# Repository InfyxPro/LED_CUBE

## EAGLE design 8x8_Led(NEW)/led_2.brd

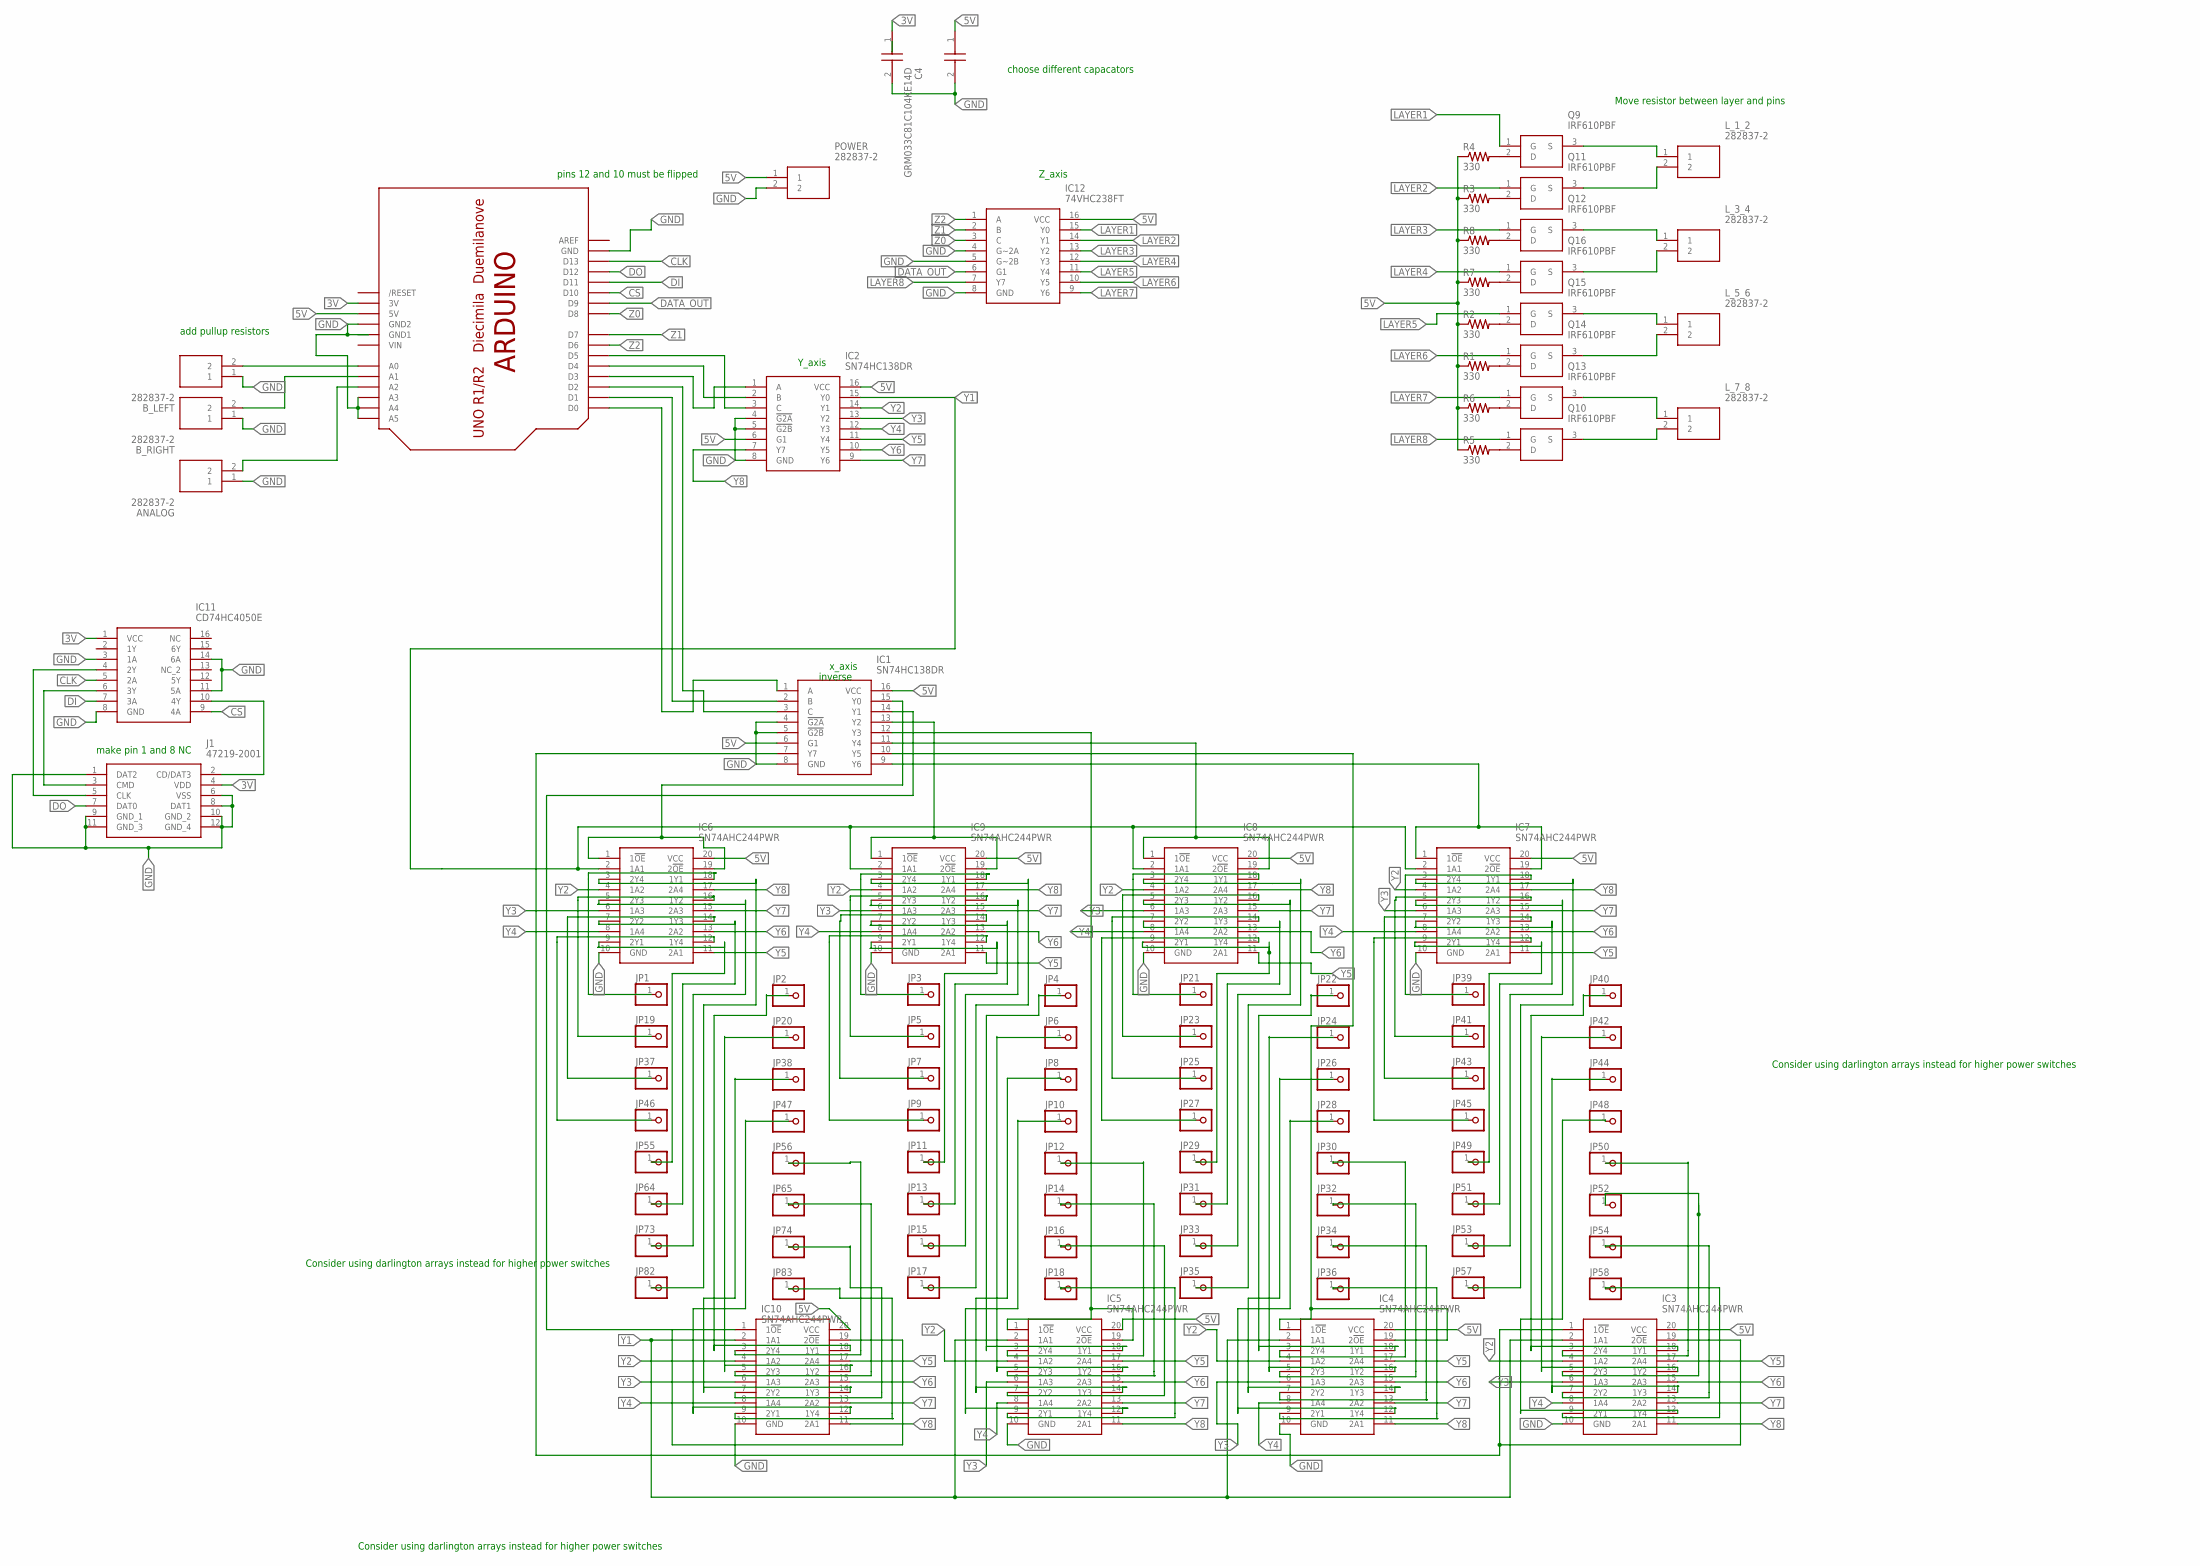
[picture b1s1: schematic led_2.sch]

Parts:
ANALOG: 282837-2; SHDR2W100P0X508_1X2_1016X820X1
B_LEFT: 282837-2; SHDR2W100P0X508_1X2_1016X820X1
B_RIGHT: 282837-2; SHDR2W100P0X508_1X2_1016X820X1
C4, C5: GRM033C81C104KE14D; CAPC0603X33N
IC1, IC2: SN74HC138DR; SOIC127P600X175-16N
IC3, IC4, IC5, IC6, IC7, IC8, IC9, IC10: SN74AHC244PWR; SOP65P640X120-20N
IC11: CD74HC4050E; DIP254P762X508-16
IC12: 74VHC238FT; SOP65P640X120-16N
J1: 47219-2001; 472192001
JP1, JP2, JP3, JP4, JP5, JP6, JP7, JP8, JP9, JP10, JP11, JP12, JP13, JP14, JP15, JP16, JP17, JP18, JP19, JP20, JP21, JP22, JP23, JP24, JP25, JP26, JP27, JP28, JP29, JP30, JP31, JP32, JP33, JP34, JP35, JP36, JP37, JP38, JP39, JP40, JP41, JP42, JP43, JP44, JP45, JP46, JP47, JP48, JP49, JP50, JP51, JP52, JP53, JP54, JP55, JP56, JP57, JP58, JP64, JP65, JP73, JP74, JP82, JP83: PINHD-1X1; 1X01
L_1_2, L_3_4, L_5_6, L_7_8: 282837-2; SHDR2W100P0X508_1X2_1016X820X1
POWER: 282837-2; SHDR2W100P0X508_1X2_1016X820X1
Q9, Q10, Q11, Q12, Q13, Q14, Q15, Q16: IRF610PBF; TO254P465X1024X2050-3P
R1, R2, R3, R4, R5, R6, R7, R8: 330; 0207/12
U$2: ARDUINO-NOHOLE

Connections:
3V: C4.1, IC11.1 (VCC), J1.4 (VDD), U$2.3V
5V: C5.1, IC1.6 (G1), IC1.16 (VCC), IC2.6 (G1), IC2.16 (VCC), IC3.20 (VCC), IC4.20 (VCC), IC5.20 (VCC), IC6.20 (VCC), IC7.20 (VCC), IC8.20 (VCC), IC9.20 (VCC), IC10.20 (VCC), IC12.16 (VCC), POWER.1, R1.1, R2.1, R3.1, R4.1, R5.1, R6.1, R7.1, R8.1, U$2.5V
CLK: IC11.5 (2A), U$2.D13
CS: IC11.9 (4A), U$2.D10
DATA_OUT: IC12.6 (G1), U$2.D9
DI: IC11.7 (3A), U$2.D11
DO: J1.7 (DAT0), U$2.D12
GND: ANALOG.1, B_LEFT.1, B_RIGHT.1, C4.2, C5.2, IC1.4 (!G2A), IC1.5 (!G2B), IC1.8 (GND), IC2.4 (!G2A), IC2.5 (!G2B), IC2.8 (GND), IC3.10 (GND), IC4.10 (GND), IC5.10 (GND), IC6.10 (GND), IC7.10 (GND), IC8.10 (GND), IC9.10 (GND), IC10.10 (GND), IC11.3 (1A), IC11.8 (GND), IC11.11 (5A), IC11.14 (6A), IC12.4 (G~2A), IC12.5 (G~2B), IC12.8 (GND), J1.1 (DAT2), J1.6 (VSS), J1.8 (DAT1), J1.9 (GND_1), J1.10 (GND_2), J1.11 (GND_3), J1.12 (GND_4), POWER.2, U$2.A3, U$2.A4, U$2.A5, U$2.GND, U$2.GND1, U$2.GND2
LAYER1: IC12.15 (Y0), Q9.1 (G)
LAYER2: IC12.14 (Y1), Q11.1 (G)
LAYER3: IC12.13 (Y2), Q12.1 (G)
LAYER4: IC12.12 (Y3), Q16.1 (G)
LAYER5: IC12.11 (Y4), Q15.1 (G)
LAYER6: IC12.10 (Y5), Q14.1 (G)
LAYER7: IC12.9 (Y6), Q13.1 (G)
LAYER8: IC12.7 (Y7), Q10.1 (G)
unnamed: IC1.9 (Y6), IC7.1 (1!OE), IC7.19 (2!OE)
unnamed: IC2.3 (C), U$2.D5
unnamed: IC6.18 (1Y1), JP1.1
unnamed: IC2.2 (B), U$2.D4
unnamed: IC6.16 (1Y2), JP19.1
unnamed: IC6.14 (1Y3), JP37.1
unnamed: IC6.12 (1Y4), JP46.1
unnamed: IC6.9 (2Y1), JP55.1
unnamed: IC6.7 (2Y2), JP64.1
unnamed: IC6.5 (2Y3), JP73.1
unnamed: IC2.1 (A), U$2.D3
unnamed: IC1.3 (C), U$2.D2
unnamed: IC1.2 (B), U$2.D1
unnamed: IC1.1 (A), U$2.D0
unnamed: B_LEFT.2, U$2.A0
unnamed: Q9.2 (D), R4.2
unnamed: Q11.2 (D), R3.2
unnamed: Q12.2 (D), R8.2
unnamed: Q16.2 (D), R7.2
unnamed: Q15.2 (D), R2.2
unnamed: Q14.2 (D), R1.2
unnamed: Q13.2 (D), R6.2
unnamed: Q10.2 (D), R5.2
unnamed: L_1_2.1, Q9.3 (S)
unnamed: L_1_2.2, Q11.3 (S)
unnamed: L_3_4.1, Q12.3 (S)
unnamed: L_3_4.2, Q16.3 (S)
unnamed: L_5_6.1, Q15.3 (S)
unnamed: L_5_6.2, Q14.3 (S)
unnamed: L_7_8.1, Q13.3 (S)
unnamed: L_7_8.2, Q10.3 (S)
unnamed: IC6.3 (2Y4), JP82.1
unnamed: IC10.18 (1Y1), JP2.1
unnamed: IC10.16 (1Y2), JP20.1
unnamed: IC10.14 (1Y3), JP38.1
unnamed: IC10.12 (1Y4), JP47.1
unnamed: IC10.3 (2Y4), JP56.1
unnamed: IC10.5 (2Y3), JP65.1
unnamed: IC10.7 (2Y2), JP74.1
unnamed: IC10.9 (2Y1), JP83.1
unnamed: IC9.18 (1Y1), JP3.1
unnamed: IC9.16 (1Y2), JP5.1
unnamed: IC9.14 (1Y3), JP7.1
unnamed: IC9.12 (1Y4), JP9.1
unnamed: IC9.9 (2Y1), JP11.1
unnamed: IC9.7 (2Y2), JP13.1
unnamed: IC9.5 (2Y3), JP15.1
unnamed: IC9.3 (2Y4), JP17.1
unnamed: IC5.18 (1Y1), JP4.1
unnamed: IC5.16 (1Y2), JP6.1
unnamed: IC5.14 (1Y3), JP8.1
unnamed: IC5.12 (1Y4), JP10.1
unnamed: IC5.3 (2Y4), JP12.1
unnamed: IC5.5 (2Y3), JP14.1
unnamed: IC5.7 (2Y2), JP16.1
unnamed: IC5.9 (2Y1), JP18.1
unnamed: IC8.18 (1Y1), JP21.1
unnamed: IC8.16 (1Y2), JP23.1
unnamed: IC8.14 (1Y3), JP25.1
unnamed: IC8.12 (1Y4), JP27.1
unnamed: IC8.9 (2Y1), JP29.1
unnamed: IC8.7 (2Y2), JP31.1
unnamed: IC8.5 (2Y3), JP33.1
unnamed: IC8.3 (2Y4), JP35.1
unnamed: IC4.18 (1Y1), JP22.1
unnamed: IC4.16 (1Y2), JP24.1
unnamed: IC4.14 (1Y3), JP26.1
unnamed: IC4.12 (1Y4), JP28.1
unnamed: IC4.3 (2Y4), JP30.1
unnamed: IC4.5 (2Y3), JP32.1
unnamed: IC4.7 (2Y2), JP34.1
unnamed: IC4.9 (2Y1), JP36.1
unnamed: IC7.18 (1Y1), JP39.1
unnamed: IC7.16 (1Y2), JP41.1
unnamed: IC7.14 (1Y3), JP43.1
unnamed: IC7.12 (1Y4), JP45.1
unnamed: IC7.9 (2Y1), JP49.1
unnamed: IC7.7 (2Y2), JP51.1
unnamed: IC7.5 (2Y3), JP53.1
unnamed: IC7.3 (2Y4), JP57.1
unnamed: IC3.18 (1Y1), JP40.1
unnamed: IC3.16 (1Y2), JP42.1
unnamed: IC3.14 (1Y3), JP44.1
unnamed: IC3.12 (1Y4), JP48.1
unnamed: IC3.3 (2Y4), JP50.1
unnamed: IC3.5 (2Y3), JP52.1
unnamed: IC3.7 (2Y2), JP54.1
unnamed: IC3.9 (2Y1), JP58.1
unnamed: IC1.15 (Y0), IC6.1 (1!OE), IC6.19 (2!OE)
unnamed: IC1.13 (Y2), IC9.1 (1!OE), IC9.19 (2!OE)
unnamed: IC1.11 (Y4), IC8.1 (1!OE), IC8.19 (2!OE)
unnamed: IC1.14 (Y1), IC10.1 (1!OE), IC10.19 (2!OE)
unnamed: IC1.7 (Y7), IC3.1 (1!OE), IC3.19 (2!OE)
unnamed: IC1.12 (Y3), IC5.1 (1!OE), IC5.19 (2!OE)
unnamed: IC1.10 (Y5), IC4.1 (1!OE), IC4.19 (2!OE)
unnamed: ANALOG.2, U$2.A2
unnamed: IC11.6 (3Y), J1.3 (CMD)
unnamed: IC11.4 (2Y), J1.5 (CLK)
unnamed: IC11.10 (4Y), J1.2 (CD/DAT3)
unnamed: B_RIGHT.2, U$2.A1
VIN: U$2.VIN
Y1: IC2.15 (Y0), IC3.2 (1A1), IC4.2 (1A1), IC5.2 (1A1), IC6.2 (1A1), IC7.2 (1A1), IC8.2 (1A1), IC9.2 (1A1), IC10.2 (1A1)
Y2: IC2.14 (Y1), IC3.4 (1A2), IC4.4 (1A2), IC5.4 (1A2), IC6.4 (1A2), IC7.4 (1A2), IC8.4 (1A2), IC9.4 (1A2), IC10.4 (1A2)
Y3: IC2.13 (Y2), IC3.6 (1A3), IC4.6 (1A3), IC5.6 (1A3), IC6.6 (1A3), IC7.6 (1A3), IC8.6 (1A3), IC9.6 (1A3), IC10.6 (1A3)
Y4: IC2.12 (Y3), IC3.8 (1A4), IC4.8 (1A4), IC5.8 (1A4), IC6.8 (1A4), IC7.8 (1A4), IC8.8 (1A4), IC9.8 (1A4), IC10.8 (1A4)
Y5: IC2.11 (Y4), IC3.17 (2A4), IC4.17 (2A4), IC5.17 (2A4), IC6.11 (2A1), IC7.11 (2A1), IC8.11 (2A1), IC9.11 (2A1), IC10.17 (2A4)
Y6: IC2.10 (Y5), IC3.15 (2A3), IC4.15 (2A3), IC5.15 (2A3), IC6.13 (2A2), IC7.13 (2A2), IC8.13 (2A2), IC9.13 (2A2), IC10.15 (2A3)
Y7: IC2.9 (Y6), IC3.13 (2A2), IC4.13 (2A2), IC5.13 (2A2), IC6.15 (2A3), IC7.15 (2A3), IC8.15 (2A3), IC9.15 (2A3), IC10.13 (2A2)
Y8: IC2.7 (Y7), IC3.11 (2A1), IC4.11 (2A1), IC5.11 (2A1), IC6.17 (2A4), IC7.17 (2A4), IC8.17 (2A4), IC9.17 (2A4), IC10.11 (2A1)
Z0: IC12.3 (C), U$2.D8
Z1: IC12.2 (B), U$2.D7
Z2: IC12.1 (A), U$2.D6

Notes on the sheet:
inverse
Y_axis
Z_axis
x_axis
pins 12 and 10 must be flipped
make pin 1 and 8 NC
add pullup resistors
choose different capacators
Move resistor between layer and pins
Consider using darlington arrays instead for higher power switches

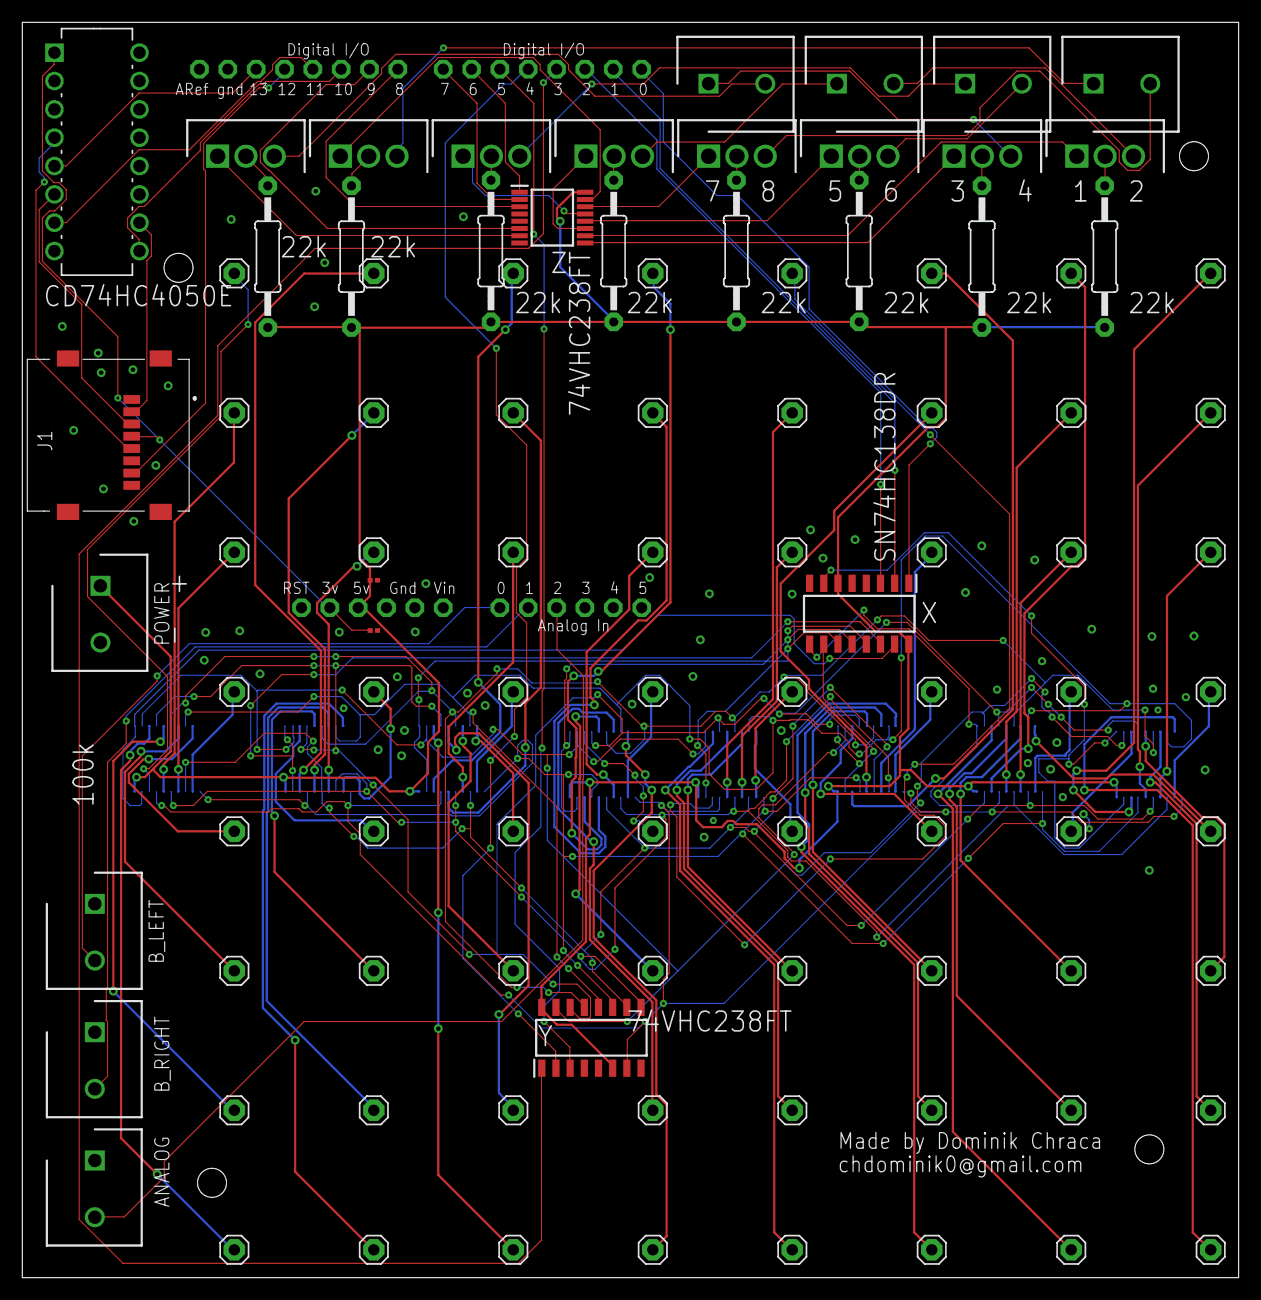
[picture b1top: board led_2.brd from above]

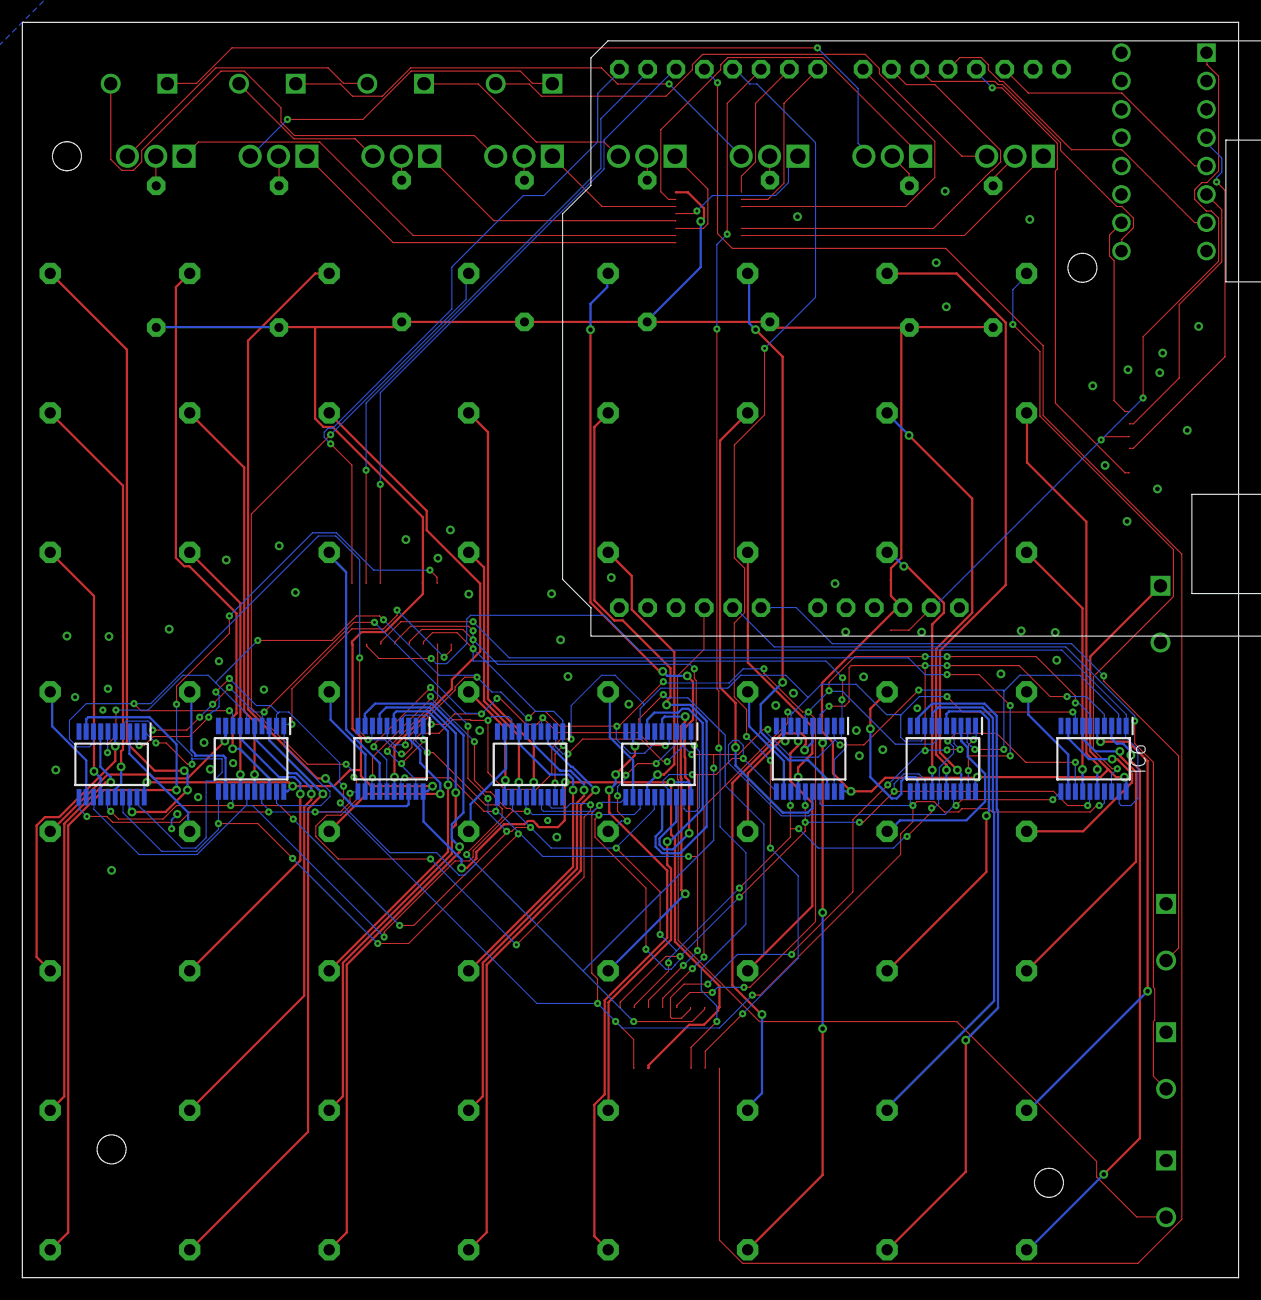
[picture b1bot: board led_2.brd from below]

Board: 2 copper layers, 109.0 x 112.5 mm, 104 parts (8 on the bottom side), 127 nets.
